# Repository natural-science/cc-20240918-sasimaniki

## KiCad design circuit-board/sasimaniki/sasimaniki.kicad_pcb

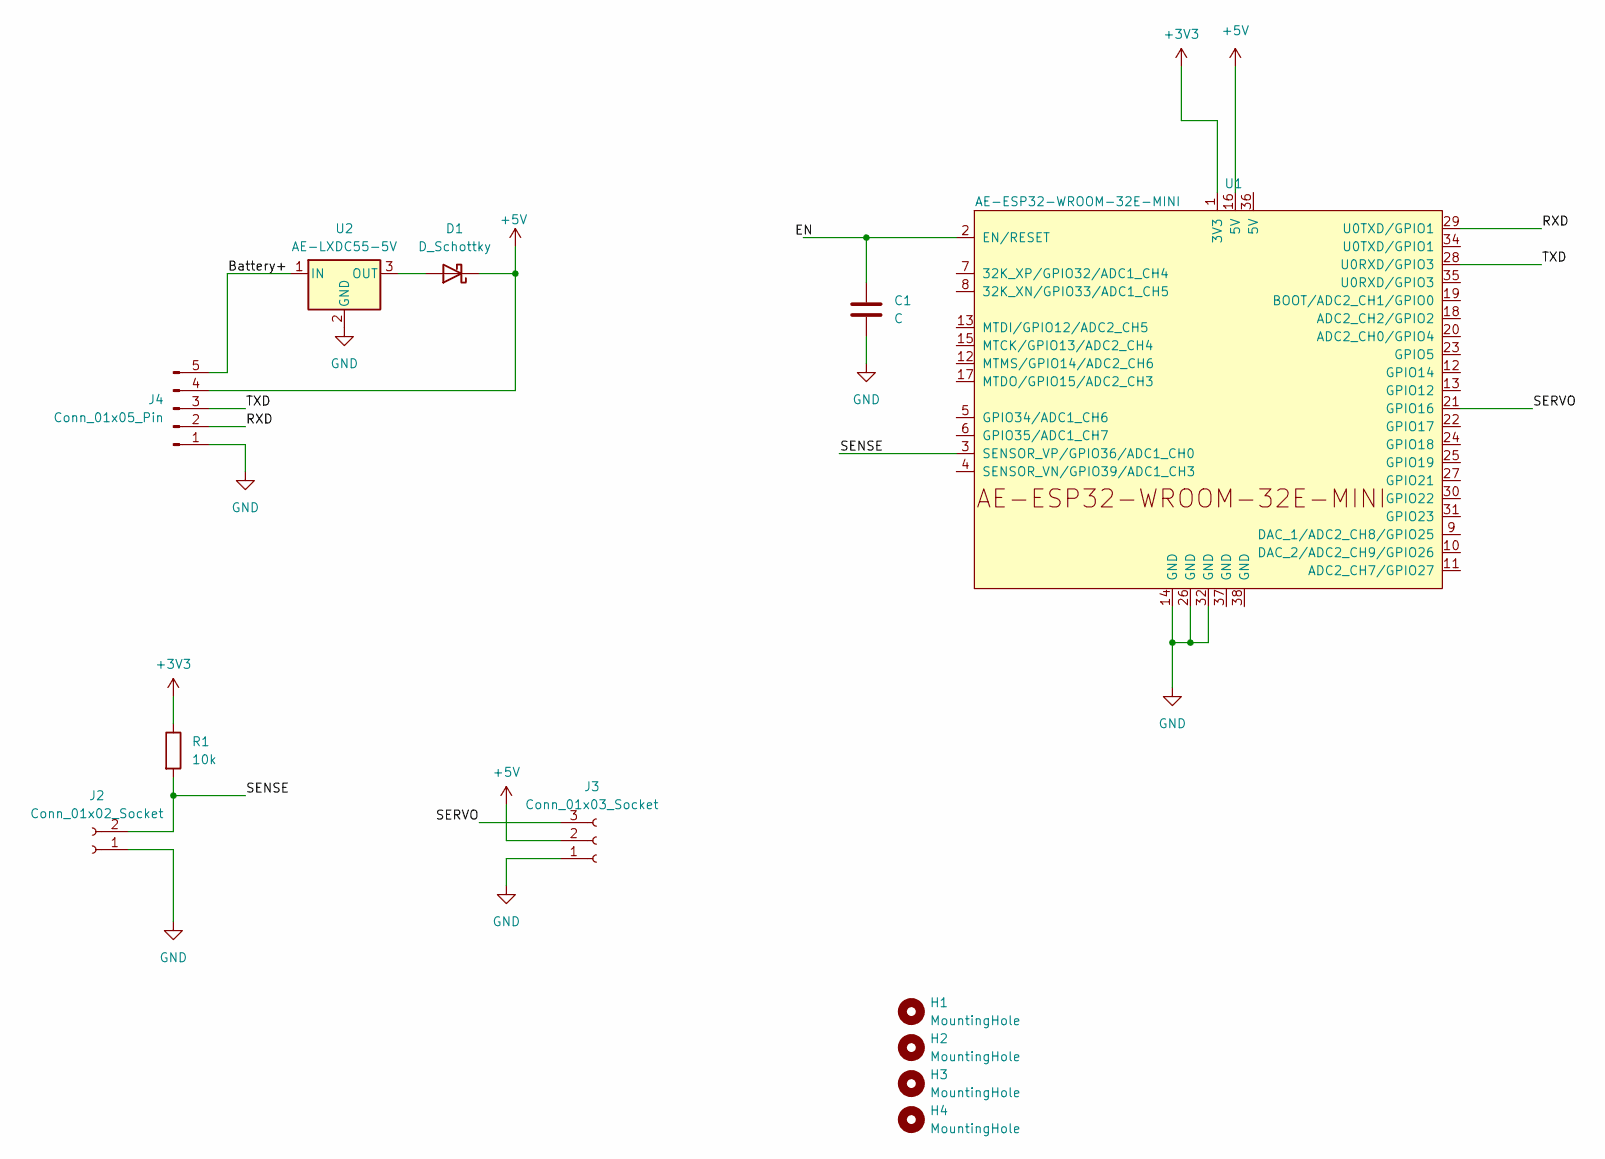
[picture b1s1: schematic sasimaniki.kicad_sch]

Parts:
C1: C; C_0603_1608Metric_Pad1.08x0.95mm_HandSolder
D1: D_Schottky; D_2114_3652Metric_Pad1.85x3.75mm_HandSolder
H1, H2, H3, H4: MountingHole; MountingHole_2.2mm_M2
J2: Conn_01x02_Socket; JST_XH_S2B-XH-A_1x02_P2.50mm_Horizontal
J3: Conn_01x03_Socket; JST_XH_S3B-XH-A_1x03_P2.50mm_Horizontal
J4: Conn_01x05_Pin; JST_XH_S5B-XH-A_1x05_P2.50mm_Horizontal
R1: 10k; R_0603_1608Metric_Pad0.98x0.95mm_HandSolder
U1: AE-ESP32-WROOM-32E-MINI
U2: AE-LXDC55-5V; AE-LXDC55

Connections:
+3V3: R1.1, U1.1 (3V3)
+5V: D1.1 (K), J3.2, J4.4, U1.16 (5V)
/Battery+: J4.5, U2.1 (IN)
/RXD: J4.2, U1.29 (U0TXD/GPIO1)
/SENSE: J2.2, R1.2, U1.3 (SENSOR_VP/GPIO36/ADC1_CH0)
/SERVO: J3.3, U1.21 (GPIO16)
/TXD: J4.3, U1.28 (U0RXD/GPIO3)
GND: C1.2, J2.1, J3.1, J4.1, U1.14 (GND), U1.26 (GND), U1.32 (GND), U2.2 (GND)
unnamed: D1.2 (A), U2.3 (OUT)
unnamed: C1.1, U1.2 (EN/RESET)

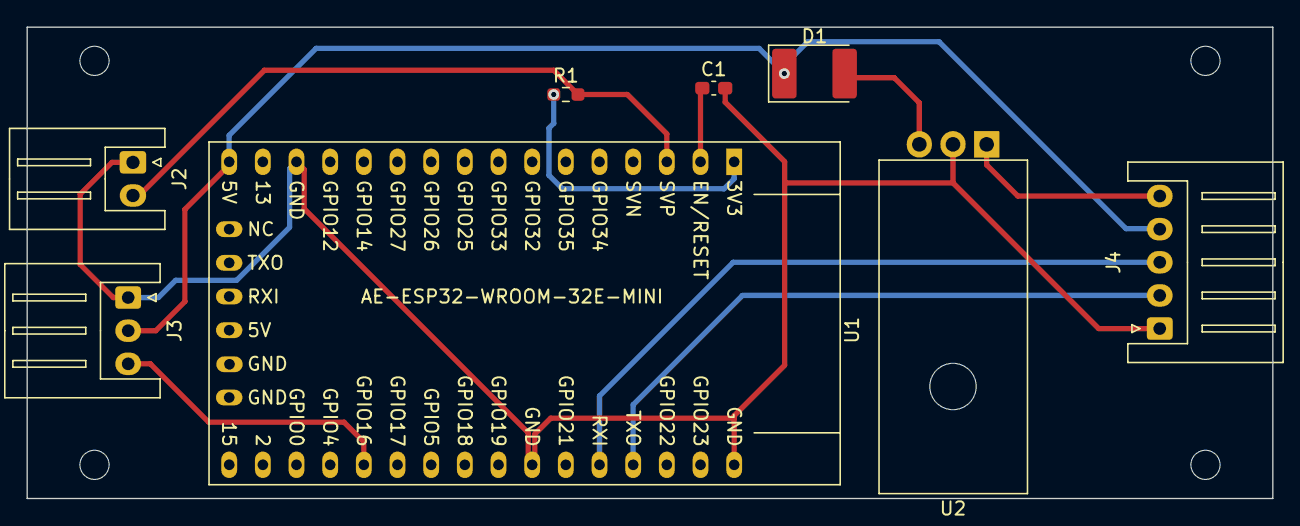
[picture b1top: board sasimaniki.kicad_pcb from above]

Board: 2 copper layers, 94.0 x 35.6 mm, 12 parts (0 on the bottom side), 10 nets.

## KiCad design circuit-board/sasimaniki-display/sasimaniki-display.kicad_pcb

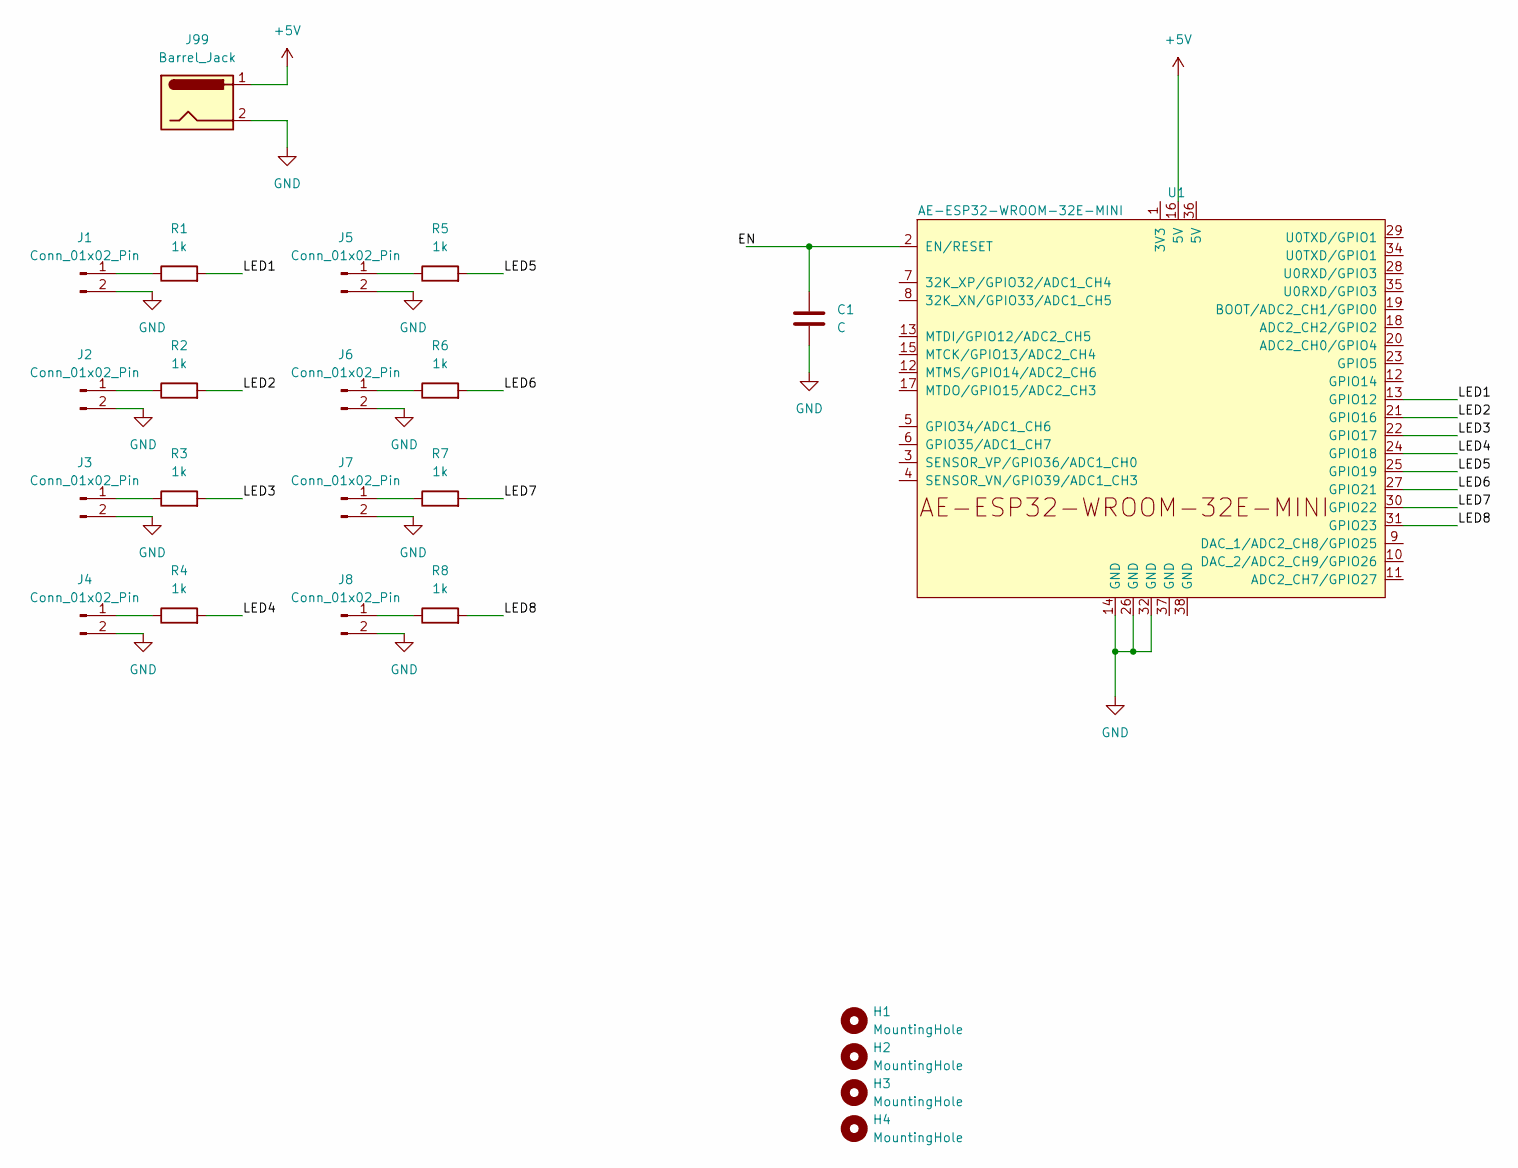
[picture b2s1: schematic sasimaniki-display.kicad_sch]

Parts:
C1: C; C_0603_1608Metric_Pad1.08x0.95mm_HandSolder
H1, H2, H3, H4: MountingHole; MountingHole_2.2mm_M2
J1, J2, J3, J4, J5, J6, J7, J8: Conn_01x02_Pin; PinHeader_1x02_P2.54mm_Vertical
J99: Barrel_Jack; BarrelJack_CUI_PJ-102AH_Horizontal
R1, R2, R3, R4, R5, R6, R7, R8: 1k; R_Axial_DIN0207_L6.3mm_D2.5mm_P10.16mm_Horizontal
U1: AE-ESP32-WROOM-32E-MINI

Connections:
+5V: J99.1, U1.16 (5V)
/LED1: R1.2, U1.13 (GPIO12)
/LED2: R2.2, U1.21 (GPIO16)
/LED3: R3.2, U1.22 (GPIO17)
/LED4: R4.2, U1.24 (GPIO18)
/LED5: R5.2, U1.25 (GPIO19)
/LED6: R6.2, U1.27 (GPIO21)
/LED7: R7.2, U1.30 (GPIO22)
/LED8: R8.2, U1.31 (GPIO23)
GND: C1.2, J1.2, J2.2, J3.2, J4.2, J5.2, J6.2, J7.2, J8.2, J99.2, U1.14 (GND), U1.26 (GND), U1.32 (GND)
unnamed: J1.1, R1.1
unnamed: J2.1, R2.1
unnamed: J3.1, R3.1
unnamed: J4.1, R4.1
unnamed: J5.1, R5.1
unnamed: J6.1, R6.1
unnamed: J7.1, R7.1
unnamed: J8.1, R8.1
unnamed: C1.1, U1.2 (EN/RESET)

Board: 2 copper layers, 23 parts (0 on the bottom side), 19 nets, no tracks yet.

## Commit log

2024-09-17 initial commit.
2024-09-17 big bang.
2024-09-20 add .gitignore and .gitattributes.
2024-09-20 add circuit-board/.
2024-09-23 add measure related embedded programs.
2024-09-24 implement bluetooth stuff in "measure" embedded program.
2024-09-26 update "measure" circuit board.
2024-09-26 add measure_test_bluetooth embbeded program.
